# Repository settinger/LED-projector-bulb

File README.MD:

# LED Replacement for DCA Lamps

In the era of film, the [DCA lamp](https://www.replacementlightbulbs.com/lampdca21v150w.html) was used in dozens of styles of home projector. Nowadays, they are quite hard to come by. And even if you do find a supplier, you'll still end up paying upwards of $100 USD for a single bulb that only lasts around 15 hours! Some people have modified their film projectors to use modern LED illumination, but this usually requires an alternate external power supply and some permanent modifications to the vintage machine. My vision is something much simpler: an LED circuit shaped like the original bulb, a true drop-in replacement!

[ <br/>*(Click to go to an interactive 3D viewer)*](https://skfb.ly/onLyB)<br/>

This is most definitely still a work-in-progress. Message me with questions/advice/suggestions/anything!

## Latest version: revision 3 (April 2021)

This is a significant change from the previous two versions. It uses a 19W Cree XHP50.2 (or XHP50) LED, and the whole upright PCB is now a single-layer aluminum-substrate PCB for better thermal management. Screw terminals are used to affix the two boards perpendicularly, and some safety features (2.5A fuse and an optional inrush current limiter) have been added. The bill of materials can be found [over here](/bom/bom.md) or in [this interactive page](/bom/ibom.html).

## Revision 2 (April 2021)
The main change between revisions 1 and 2 is the LED driver itself. I switched from the AL8860 IC to the PAM2863 because the AL8860 is out of stock friggin' EVERYWHERE right now. I also did away with the 15V LDO; why did I even put that on there in the first place? In its place is a tiny 3.3V LDO to power the dimmer controls. This design still uses the same LED module. I did not fix the incorrect light center distance. Instead, I overhauled the PCB to make Revision 3.

## Revision 1 (November 2020)
My first attempt at a DCA replacement. It uses a no-brand 10W LED module that is (was?) prevalent on eBay. The AC-to-DC rectifying capacitors are 16 mm in diameter, and protrude over the edge of the base PCB. This prevented them from sitting properly in my test projector (an Argos Showmaster 750A). Even if it were to fit in the socket, the light center distance on this PCB is a 1/4 inch too high, which is substantial. The dimming circuit did not behave the way I was expecting; at low control voltages the LED would flash on and off around 0.5 Hz, instead of getting dimmer.

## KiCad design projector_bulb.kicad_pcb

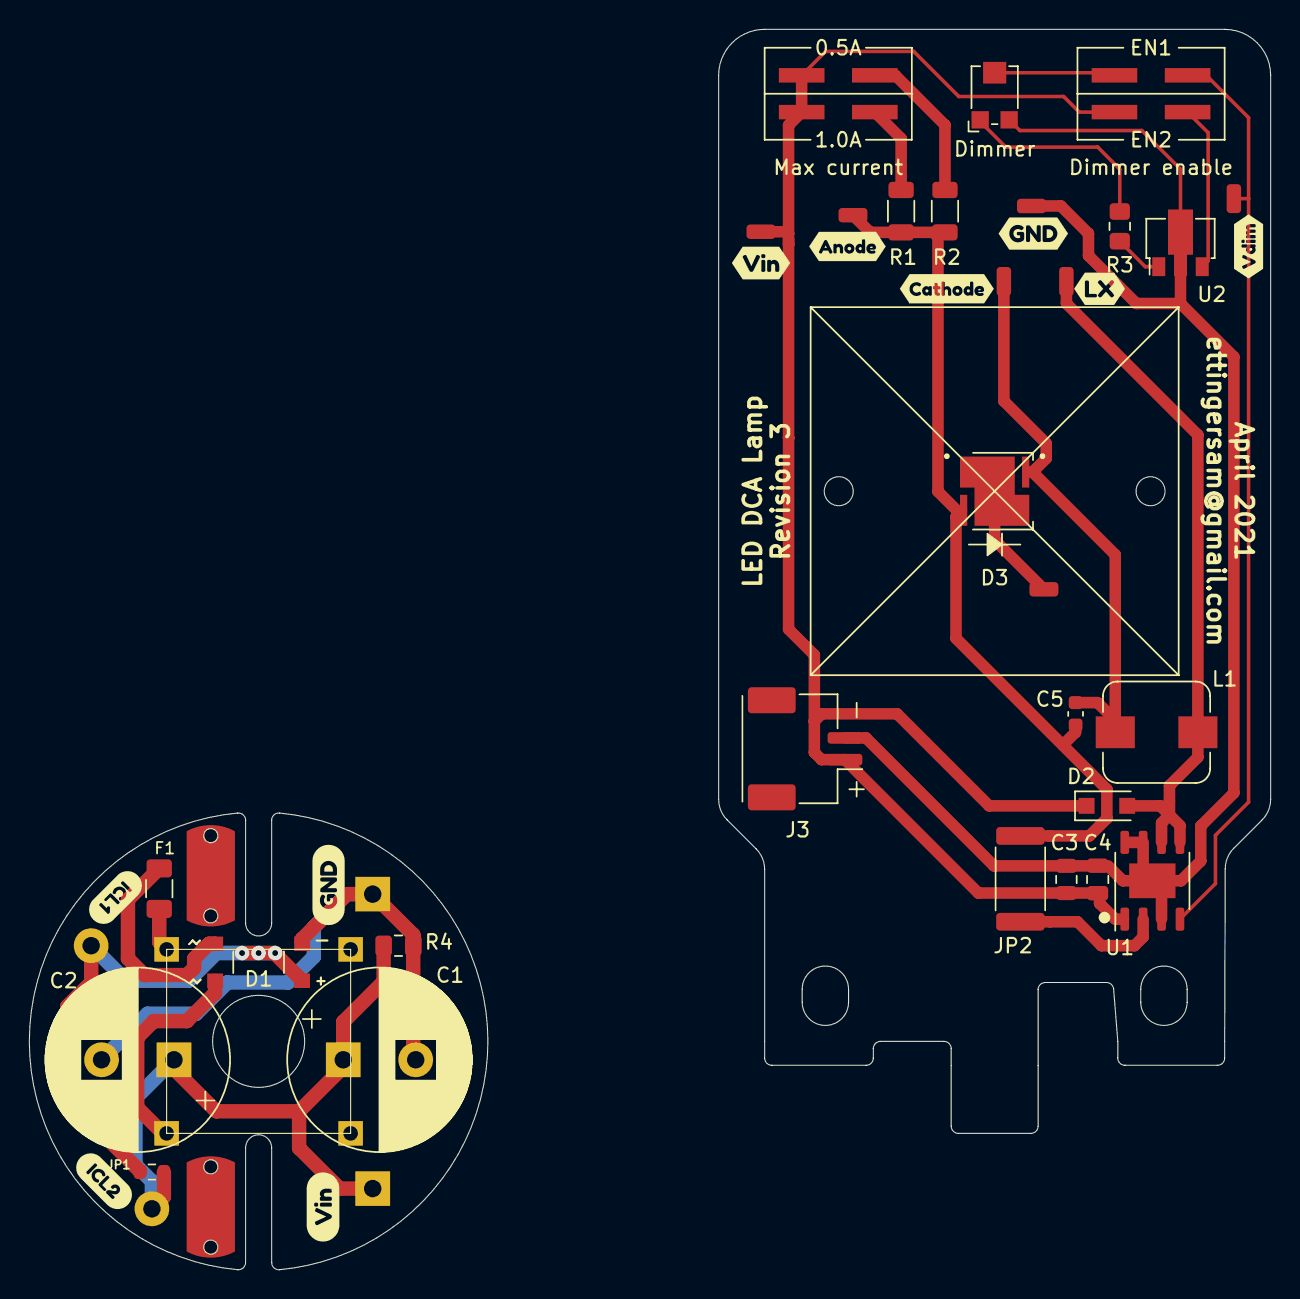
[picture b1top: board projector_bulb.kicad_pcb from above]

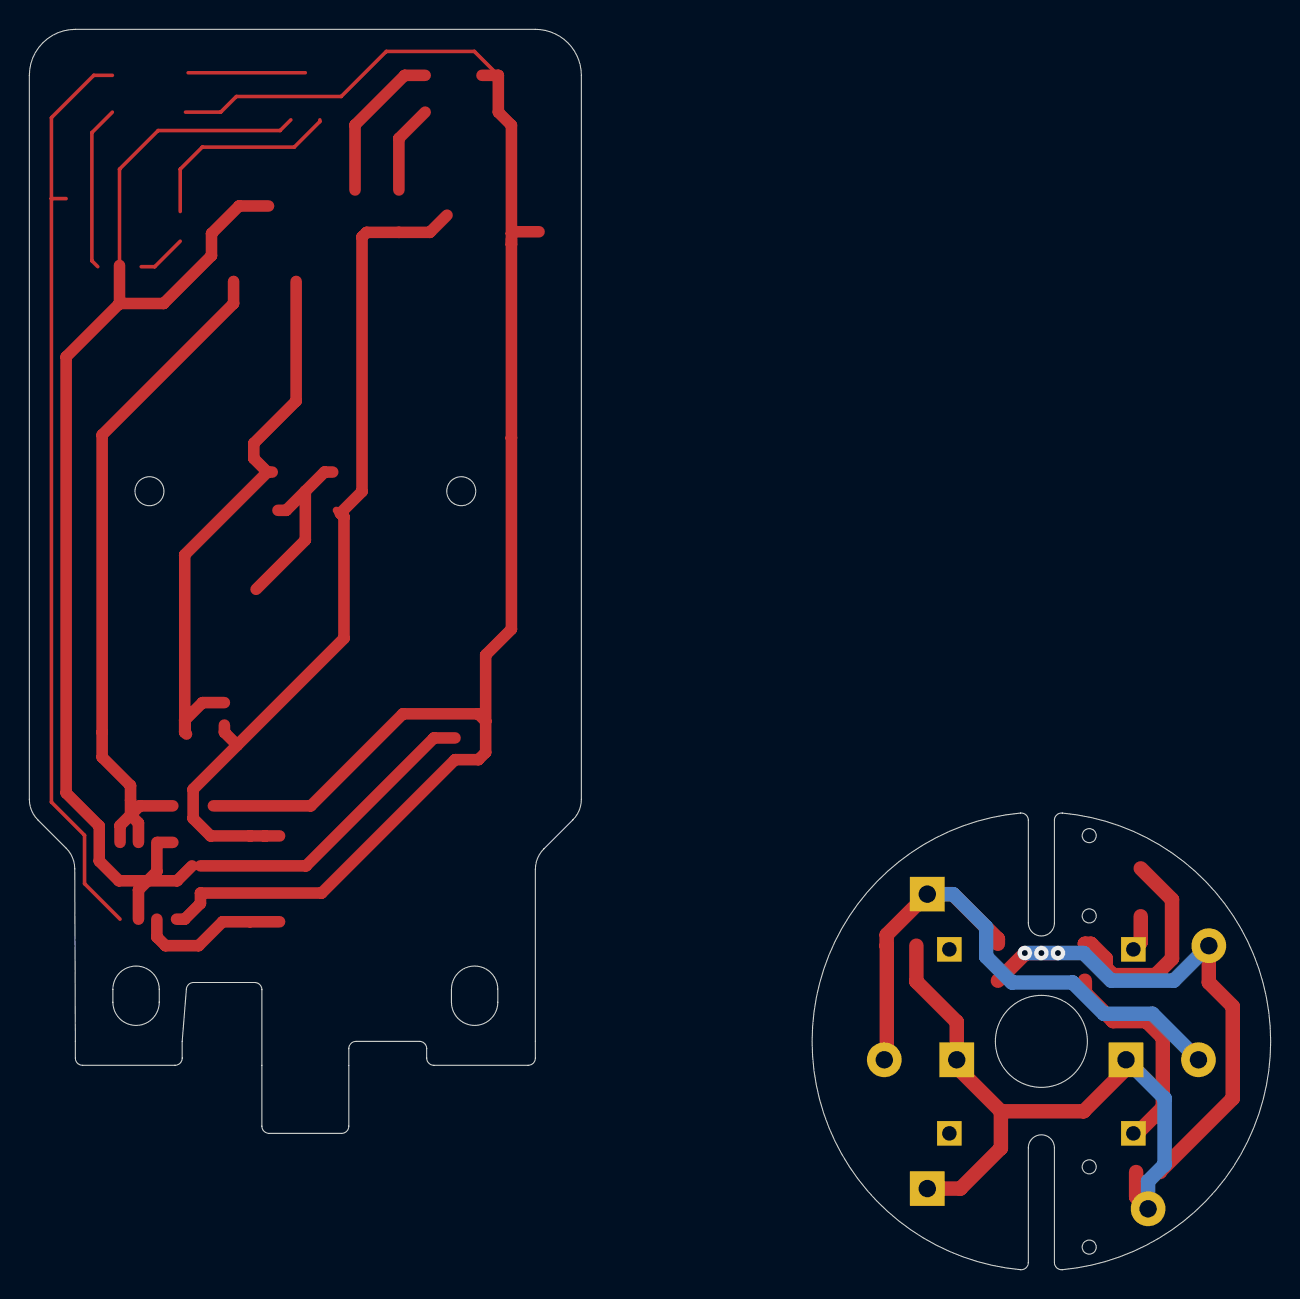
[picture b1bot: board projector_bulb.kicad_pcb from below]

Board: 2 copper layers, 85.7 x 85.6 mm, 47 parts (2 on the bottom side), 20 nets.

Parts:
C1, C2: 1000μ; CP_Radial_D12.5mm_P5.00mm
C3, C4: 10μ; C_0805_2012Metric
C5: 1μ; C_0603_1608Metric
D1: Bridge Rectifier; Diode_Bridge_Comchip_2A
D2: Schottky; D_SOD-123F
D3: LED; LED_Cree-XHP50_12V
F1: Fuse; Fuse_1206_3216Metric
H1, H2: MountingHole; wuerth_7466313R
HS1: Heatsink; Heatsink_35x35x18mm
J1: to_upright_+; TestPoint_THTPad_3.0x3.0mm_Drill1.5mm
J2: to_upright_-; TestPoint_THTPad_3.0x3.0mm_Drill1.5mm
J3: to_base; Molex_CLIK-Mate_505405-0270_1x02-1MP_P1.50mm_Vertical
J4, J5: Conn_02x02_Odd_Even; PinHeader_2x02_P2.54mm_Vertical_SMD
JP1: ICL Bypass; R_0603_1608Metric
JP2: Jumper_NC_Small; R_2512_6332Metric
L1: 47μ; panasonic_PCC-M0748M
LA1: Lamp; GX17q
LENS1: Lens; LENS_LEDIL_CA16370_HB-SQ-W
R1: 0.200; R_1206_3216Metric
R2: 0.100; R_1206_3216Metric
R3: 7.5k; R_0805_2012Metric_Pad1.15x1.40mm_HandSolder
R4: 1M; R_0805_2012Metric_Pad1.15x1.40mm_HandSolder
RV1: 10k; Potentiometer_Bourns_TC33X_Vertical
TH1: Thermistor_NTC; RV_Disc_D21.5mm_W4.3mm_P10mm
TP1, TP2, TP3, TP4, TP5, TP6, TP7: TestPoint; Test_Point_0603
U1: PAM2863; HTSOP-8-1EP_3.9x4.9mm_P1.27mm_EP2.4x3.2mm
U2: AP7381-33Y; SOT-89-3
svg2mod, svg2mod#2, svg2mod#3, svg2mod#4, svg2mod#5, svg2mod#6, svg2mod#7, svg2mod#8, svg2mod#9, svg2mod#10: G***; label

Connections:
DIMMING: J5.1, TP4.1, U1.4
GND_BASE: C1.2, C2.2, D1.2, J2.1, R4.2
GND_UPRIGHT: C3.1, C4.1, J3.2, RV1.3, TP2.1, U1.3, U1.7, U1.8, U1.9, U2.2
unnamed: C5.1, D3.1, L1.1, TP6.1
unnamed: C5.2, D3.2, JP2.2, R1.2, R2.2, TP5.1
unnamed: D1.1, JP1.1, TH1.2
unnamed: D1.3, F1.1
unnamed: D1.4, LA1.1
unnamed: D2.2, L1.2, TP3.1, U1.5, U1.6
unnamed: D3.3, TP7.1
unnamed: F1.2, LA1.2
unnamed: J4.2, R2.1
unnamed: J4.4, R1.1
unnamed: J5.2, RV1.2
unnamed: J5.4, U2.3
unnamed: JP2.1, U1.2
unnamed: R3.1, RV1.1
unnamed: R3.2, U2.1
VIN_BASE: C1.1, C2.1, J1.1, JP1.2, R4.1, TH1.1
VIN_UPRIGHT: C3.2, C4.2, D2.1, J3.1, J4.1, J4.3, J5.3, TP1.1, U1.1

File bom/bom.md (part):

# Bill of Materials
## Revision 3

## Base PCB BOM

|      | References                   | Value                      | Footprint          | Quantity | Digi-Key Part Number | Notes                             |
|------|------------------------------|----------------------------|--------------------|----------|---------------------|-----------------------------------|
| 1    | R4                           | 1 MΩ                       | 0805 (2012 Metric) | 1        | [RMCF0805JT1M20CT-ND‎](https://www.digikey.com/product-detail/en/RMCF0805JT1M20/RMC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 | |
| 2    | JP1                          | 0 Ω                        | 0603 (1608 Metric) | 1        | [36-5110CT-ND‎](https://www.digikey.com/product-detail/en/5110/36-5110CT-ND/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 | Rated for at least 3 A. Do not use if you are using an inrush current limiter (TH1). |
| 3    | C1, C2                       | 1000 μF                    | ⌀ 12.5 mm, 5 mm pitch | 1     | [UHD1V102MHD-ND‎](https://www.digikey.com/product-detail/en/UHD1V102MHD/UHD1V1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 | Rated for at least 1.5 A ripple current; must be less than 25.4 mm high to accommodate the lens and heatsink. |
| 4    | D1                           | Bridge Rectifier           | TO-269AA           | 1        | [641-1432-1-ND‎](https://www.digikey.com/product-detail/en/CDBHM2100L-HF/641-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 | I<sub>F(AV)</sub> ≥ 2 A, V<sub>RRM</sub> ≥ 40 V. |
| 5    | F1                           | 2.5 A Slow Blow            | 1206 (3216 Metric) | 1        | [507-1895-1-ND‎](https://www.digikey.com/product-detail/en/0685T2500-01/507-1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 | I've never had to pick a fuse for an AC load before, I have very little confidence in this fuse selection. |
| 6    | LA1                          | Lamp base                  | GX17q              | 1        | | It's just four header pins. |
| 7   | J1, J2                       | Molex CLIK-Mate 1.50 mm Cable Assembly | Off-board | 0.5    | [WM22838-ND‎](https://www.digikey.com/product-detail/en/0151350203/WM22838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 | Cut cable assembly in half, solder bare wires to J1 and J2 on base PCB, plug the connector into J3. |
| 8    | H1, H2                       | Würth Redcube Screw Terminal | 7.0×4.3 mm       | 2        | [732-10897-1-ND](https://www.digikey.com/en/products/detail/w%C3%BCrth-elektr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 | |
| 9    | TH1                          | 5 Ω 5 A NTC Thermistor     | Off-board          | 1        | [495-2100-ND‎](https://www.digikey.com/product-detail/en/B57237S0509M000/49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 | Inrush current limiter, might not be necessary. Do not solder JP1 if you plan to use TH1. |
| 10   | *[no designator]*            | M3 bolt, 6mm length        | Off-board          | 2        | | Attaches upright PCB at terminals H1, H2. |

## Upright PCB BOM

|      | References                   | Value                      | Footprint          | Quantity | Digi-Key Part Number | Notes                             |
|------|------------------------------|----------------------------|--------------------|----------|---------------------|-----------------------------------|
| 1    | R1                           | 0.100 Ω                    | 1206 (3216 Metric) | 1        | [273-KDV12FR100ETCT-ND‎](https://www.digikey.com/product-detail/en/KDV12FR100ET/273-K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 | |
| 2    | R2                           | 0.200 Ω                    | 1206 (3216 Metric) | 1        | [273-KDV12FR200ETCT-ND‎](https://www.digikey.com/product-detail/en/KDV12FR200ET/273-K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 | |
| 3    | R3                           | 7.5 kΩ                     | 0805 (2012 Metric) | 1        | [2019-RK73H2ATTD7501FCT-ND‎](https://www.digikey.com/product-detail/en/RK73H2ATTD7501F/20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 | |
| 4    | JP2                          | 0 Ω                        | 2512 (6432 Metric) | 1        | [CR2512-J/-000ELFCT-ND‎](https://www.digikey.com/product-detail/en/CR2512-J%2f-000ELF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 | Rated for at least 2 A. |
| 5    | C3, C4                       | 10 μF                      | 0805 (2012 Metric) | 2        | [490-10515-1-ND‎](https://www.digikey.com/product-detail/en/GRM21BR6YA106ME43L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 | |
| 6    | C5                           | 1 μF                       | 0805 (2012 Metric) | 1        | [1276-2926-1-ND‎](https://www.digikey.com/product-detail/en/CL21B105KAFNFNE/12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 | Optional capacitor to smooth output ripple. |
| 7    | L1                           | 47 μH                      | 7.4×7.0 mm         | 1        | [P124172CT-ND‎](https://www.digikey.com/product-detail/en/ETQ-P4M470KFM/P124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 | Any value between 33 μH and 120 μH should be fine. |
| 8    | RV1                          | 10 kΩ                      | TC33X              | 1        | [TC33X-103ECT-ND‎](https://www.digikey.com/product-detail/en/TC33X-2-103E/TC33X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 | |
| 9    | D2                           | LED                        | 2020 (5050 Metric) | 1        | [XHP50B-00-0000-0D0BJ250ECT-ND‎](https://www.digikey.com/product-detail/en/XHP50B-00-0000-0D0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 (cool white) or [XHP50A-00-0000-0D0HG430HCT-ND‎](https://www.digikey.com/product-detail/en/XHP50A-00-0000-0D0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 (warm white) | Cree XHP50 or XHP50.2 White LED. |
| 10   | D3                           | Schottky 3 A 40 V          | SOD-123W           | 1        | [1655-1591-1-ND‎](https://www.digikey.com/product-detail/en/SK34ATR/1655-1591-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 | |
| 11   | U1                           | PAM2863                    | SOIC-8 Exposed Pad | 1        | [PAM2863ECRDICT-ND‎](https://www.digikey.com/product-detail/en/PAM2863ECR/PAM2863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 | [Datasheet](https://www.diodes.com/assets/Datasheets/PAM2863.pdf) |
| 12   | U2                           | AP7381-33Y-13              | SOT-89-3 (TO-243AA)| 1        | [AP7381-33Y-13DICT-ND‎](https://www.digikey.com/product-detail/en/AP7381-33Y-13/AP73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 | Ensure the regulator is rated to handle more than 30 V input. |
| 13   | J3                           | Molex CLIK-Mate 2-position | 1.50 mm pitch      | 1        | [WM14459CT-ND‎](https://www.digikey.com/product-detail/en/5025840260/WM14459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 | The footprint should work for vertical- or horizontal-insert sockets. |
| 14   | J4, J5                       | 2x2 SMD Pin Header         | SMD 2.52 mm pitch  | 2        | [WM9514-ND‎](https://www.digikey.com/product-detail/en/0015912040/WM9514-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 | |
| 15   | HS1                          | Heatsink                   | 35×35×18 mm        | 1        | [HS396-ND‎](https://www.digikey.com/product-detail/en/374724B00032G/HS39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 | How big should it be? Do I need a fan? |
| 16   | TP1, TP2, TP3, TP4, TP5, TP6 | Test Point                 | 0603 (1608 Metric) | 6        | [2019-RCUCTECT-ND‎](https://www.digikey.com/product-detail/en/RCUCTE/2019-RCUCTE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 | Optional. |
| 17   | LENS1                        | LEDiL Lens HB-SQ-W         | 25×25 mm           | 1        | [711-1589-ND‎](https://www.digikey.com/product-detail/en/C16369_HB-SQ-W/711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 | Is this necessary? Who knows. |
| 18   | *[no designator]*            | 2.54 mm pin header shunts  | Off-board          | 4        | [609-861410021H11LF-ND‎](https://www.digikey.com/product-detail/en/861410021H11LF/609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 | Used for setting the max current (J4) and enabling the dimmer function (J5). |

## Combined BOM

|      | References                   | Value                      | Footprint          | Quantity | Digi-Key Part Number | Notes                             |
|------|------------------------------|----------------------------|--------------------|----------|---------------------|-----------------------------------|
| 1    | R1                           | 0.100 Ω                    | 1206 (3216 Metric) | 1        | [273-KDV12FR100ETCT-ND‎](https://www.digikey.com/product-detail/en/KDV12FR100ET/273-K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 | |
| 2    | R2                           | 0.200 Ω                    | 1206 (3216 Metric) | 1        | [273-KDV12FR200ETCT-ND‎](https://www.digikey.com/product-detail/en/KDV12FR200ET/273-K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 | |
| 3    | R3                           | 7.5 kΩ                     | 0805 (2012 Metric) | 1        | [2019-RK73H2ATTD7501FCT-ND‎](https://www.digikey.com/product-detail/en/RK73H2ATTD7501F/20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 | |
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
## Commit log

2021-04-16 Revision 2, still needs documentation and things
2021-04-20 Much progress on Aluminum PCB
2021-04-21 More changes, about to add some safety circuitry
2021-04-21 Cleaned up schematic, working on documentation next
2021-04-24 Add test points, replaced some expensive components with cheaper alternatives
2021-04-25 Making edits
2021-04-25 Routing optimizations
2021-04-26 About to attempt KiCad StepUp, wish me luck
2021-04-26 Added fillets after much blood sweat and tears
2021-04-27 BOM and readme updated
2021-04-29 Locking in revision 3 finally; moved the optional ICL to a place where I can treat it like a test point
2021-05-19 Add test point for thermal pad of LED
2021-05-21 Changed all references of 7466310R to 7466313R
2021-05-21 Changed all references of 7466310R to 7466313R (for real this time)
